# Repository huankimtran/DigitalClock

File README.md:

# DigitalClock
Code, PCB layout and schematic for a digital clock

Working video
https://www.facebook.com/HuanKimTran/videos/448578368496452/?hc_location=ufi

Project images

https://www.facebook.com/media/set/?set=a.436338533053769&type=1&l=68016e3bc0

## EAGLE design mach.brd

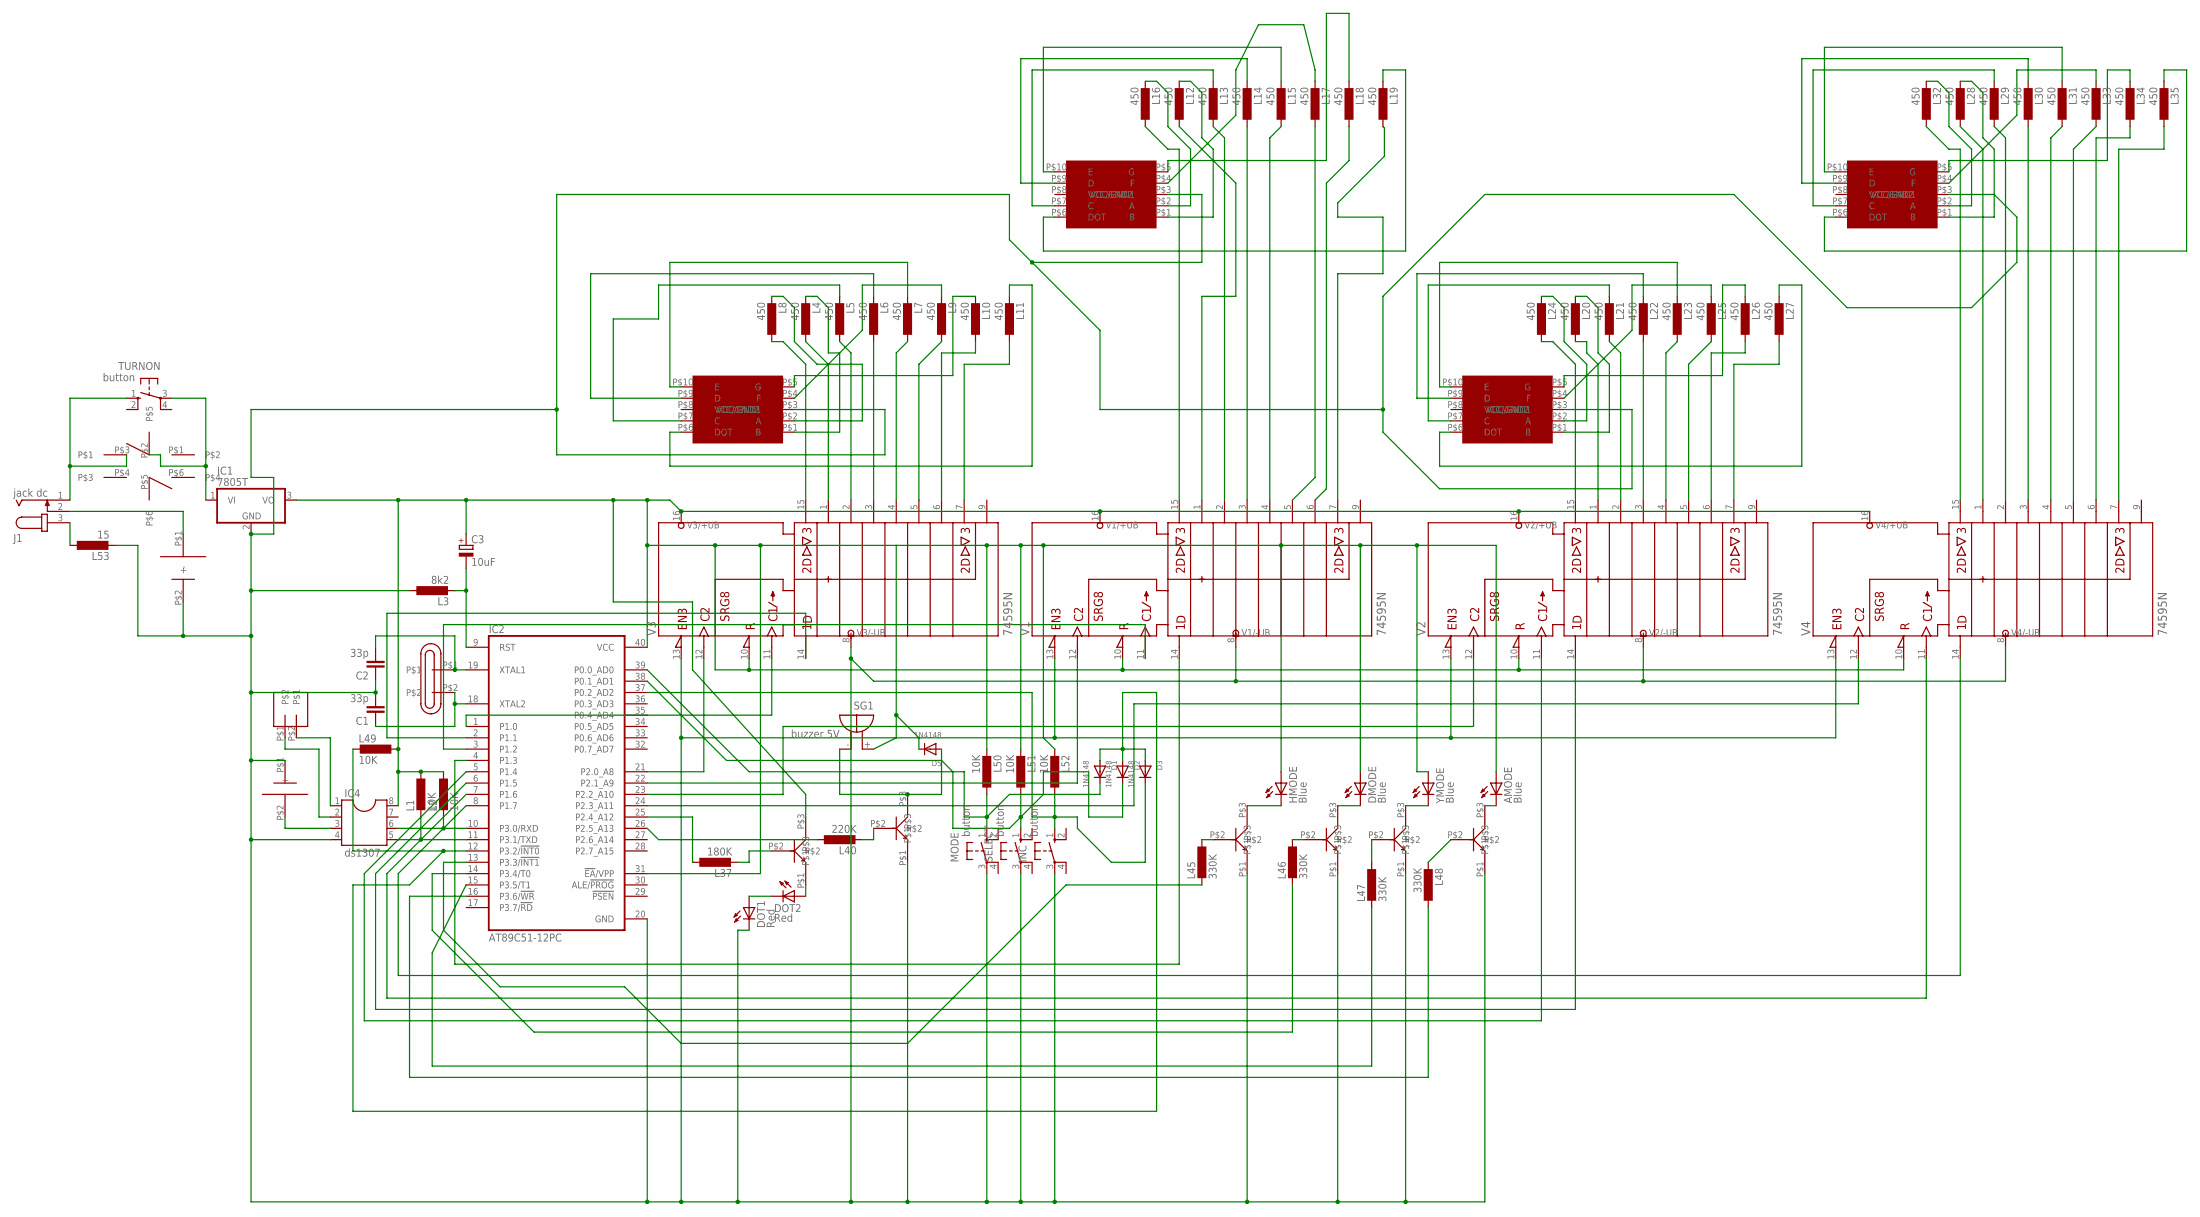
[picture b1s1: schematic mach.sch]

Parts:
7SEG1, 7SEG2, 7SEG3, 7SEG4: 7SEG13X19 common Katot; 7SEG13X19
AMODE: Blue; LED5MM
C1, C2: 33p; C5B3
C3: 10uF; E2-5
D1, D2, D3, D5: 1N4148; DO-1N4148
DMODE: Blue; LED5MM
DOT1, DOT2: Red; LED5MM
HMODE: Blue; LED5MM
IC1: 7805T; TO220H
IC2: AT89C51-12PC; DIL40
IC4: ds1307; DIL08
INC: button; B3F-10XX
J1: jack dc; SPC4077
L1, L2, L49, L50, L51, L52: 10K; 0207/10
L3: 8k2; 0207/10
L4, L5, L6, L7, L8, L9, L10, L11, L12, L13, L14, L15, L16, L17, L18, L19, L20, L21, L22, L23, L24, L25, L26, L27, L28, L29, L30, L31, L32, L33, L34, L35: 450; 0207/10
L37: 180K; 0207/10
L40: 220K; 0207/10
L45, L46, L47, L48: 330K; 0207/10
L53: 15; 0207/10
MODE: button; B3F-10XX
SELECT: button; B3F-10XX
SG1: buzzer 5V; BMT1205XH7.5
TURNON: button; B3F-10XX
U$1: PINCMOS3VCR23
U$2: XTAL32KHZMINI
U$5: XTAL12MHZ
U$7: lock button down; PUSKLOCKBUTTON
U$8, U$9, U$10, U$11, U$12, U$13: C9014
U$14: 9V; 9VBATERYJACK
V1, V2, V3, V4: 74595N; DIL16
YMODE: Blue; LED5MM

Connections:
ET: J1.2, U$14.P$1 (+)
GND: 7SEG1.P$3 (VCC/GND1), 7SEG2.P$3 (VCC/GND1), 7SEG3.P$3 (VCC/GND1), 7SEG4.P$3 (VCC/GND1), C1.2, C2.1, DOT1.K (C), IC1.2 (GND), IC2.20 (GND), IC4.4, INC.3, L3.1, L53.2, MODE.3, SELECT.3, U$1.P$1 (-), U$8.P$1, U$9.P$1, U$10.P$1, U$11.P$1, U$12.P$1, U$14.P$2 (-), V1.8 (-UB), V1.13 (!G), V2.8 (-UB), V2.13 (!G), V3.8 (-UB), V3.13 (!G), V4.8 (-UB), V4.13 (!G)
unnamed: IC2.11 (P3.1/TXD), IC4.5, L1.2
unnamed: IC2.10 (P3.0/RXD), IC4.6, L2.2
unnamed: IC4.1, U$2.P$2
unnamed: C3.-, IC2.9 (RST), L3.2
unnamed: IC4.3, U$1.P$2 (+)
unnamed: IC4.2, U$2.P$1
unnamed: C2.2, IC2.19 (XTAL1), U$5.P$1
unnamed: C1.1, IC2.18 (XTAL2), U$5.P$2
unnamed: D1.C, IC2.39 (P0.0_AD0), L50.1, MODE.1 (S)
unnamed: IC2.25 (P2.4_A12), L37.1
unnamed: IC2.1 (P1.0), V3.11 (SRCK)
unnamed: IC2.2 (P1.1), V3.14 (SER)
unnamed: IC2.3 (P1.2), V1.11 (SRCK)
unnamed: DOT2.A, U$13.P$1
unnamed: IC2.5 (P1.4), V2.11 (SRCK)
unnamed: 7SEG1.P$4 (F), L9.2
unnamed: IC2.6 (P1.5), V2.14 (SER)
unnamed: IC2.7 (P1.6), V4.11 (SRCK)
unnamed: IC2.8 (P1.7), V4.14 (SER)
unnamed: L4.1, V3.1 (QB)
unnamed: L8.1, V3.15 (QA)
unnamed: 7SEG1.P$10 (E), L7.2
unnamed: L9.1, V3.5 (QF)
unnamed: L10.1, V3.6 (QG)
unnamed: 7SEG1.P$1 (B), L4.2
unnamed: L11.1, V3.7 (QH)
unnamed: L6.1, V3.3 (QD)
unnamed: L7.1, V3.4 (QE)
unnamed: L5.1, V3.2 (QC)
unnamed: DOT1.A, DOT2.K (C)
unnamed: J1.1, TURNON.1 (S), U$7.P$3
unnamed: 7SEG1.P$5 (G), L10.2
unnamed: IC2.4 (P1.3), V1.14 (SER)
unnamed: 7SEG1.P$6 (DOT), L11.2
unnamed: IC1.1 (VI), TURNON.3, U$7.P$2
unnamed: 7SEG2.P$10 (E), L15.2
unnamed: L13.1, V1.2 (QC)
unnamed: L14.1, V1.3 (QD)
unnamed: L15.1, V1.4 (QE)
unnamed: L17.1, V1.5 (QF)
unnamed: 7SEG2.P$5 (G), L18.2
unnamed: L18.1, V1.6 (QG)
unnamed: L16.1, V1.15 (QA)
unnamed: 7SEG2.P$2 (A), L16.2
unnamed: 7SEG2.P$7 (C), L13.2
unnamed: 7SEG2.P$9 (D), L14.2
unnamed: 7SEG2.P$6 (DOT), L19.2
unnamed: L37.2, U$13.P$2
unnamed: 7SEG3.P$10 (E), L23.2
unnamed: L27.1, V2.7 (QH)
unnamed: L25.1, V2.5 (QF)
unnamed: L26.1, V2.6 (QG)
unnamed: 7SEG3.P$6 (DOT), L27.2
unnamed: L23.1, V2.4 (QE)
unnamed: L21.1, V2.2 (QC)
unnamed: L20.1, V2.1 (QB)
unnamed: L24.1, V2.15 (QA)
unnamed: 7SEG3.P$2 (A), L24.2
unnamed: 7SEG3.P$1 (B), L20.2
unnamed: 7SEG3.P$7 (C), L21.2
unnamed: 7SEG3.P$9 (D), L22.2
unnamed: 7SEG3.P$4 (F), L25.2
unnamed: 7SEG3.P$5 (G), L26.2
unnamed: L22.1, V2.3 (QD)
unnamed: 7SEG4.P$10 (E), L31.2
unnamed: L35.1, V4.7 (QH)
unnamed: L33.1, V4.5 (QF)
unnamed: L34.1, V4.6 (QG)
unnamed: L30.1, V4.3 (QD)
unnamed: L31.1, V4.4 (QE)
unnamed: L29.1, V4.2 (QC)
unnamed: L28.1, V4.1 (QB)
unnamed: L32.1, V4.15 (QA)
unnamed: 7SEG4.P$2 (A), L32.2
unnamed: 7SEG4.P$1 (B), L28.2
unnamed: 7SEG4.P$7 (C), L29.2
unnamed: 7SEG4.P$9 (D), L30.2
unnamed: 7SEG4.P$4 (F), L33.2
unnamed: 7SEG4.P$5 (G), L34.2
unnamed: 7SEG4.P$6 (DOT), L35.2
unnamed: IC2.26 (P2.5_A13), L40.1
unnamed: L40.2, U$8.P$2
unnamed: L45.1, U$10.P$2
unnamed: L46.1, U$9.P$2
unnamed: L47.1, U$11.P$2
unnamed: HMODE.K (C), U$10.P$3
unnamed: D5.A, SG1.-, U$8.P$3
unnamed: D3.C, IC2.37 (P0.2_AD2), INC.1 (S), L52.1
unnamed: L48.2, U$12.P$2
unnamed: AMODE.K (C), U$12.P$3
unnamed: U$11.P$3, YMODE.K (C)
unnamed: DMODE.K (C), U$9.P$3
unnamed: IC2.13 (P3.3/!INT1), L45.2
unnamed: D1.A, D2.A, D3.A, IC2.12 (P3.2/!INT0), L49.2
unnamed: IC2.14 (P3.4/T0), L46.2
unnamed: IC2.15 (P3.5/T1), L47.2
unnamed: IC2.16 (P3.6/!WR), L48.1
unnamed: IC2.21 (P2.0_A8), V3.12 (RCK)
unnamed: IC2.22 (P2.1_A9), V1.12 (RCK)
unnamed: IC2.23 (P2.2_A10), V2.12 (RCK)
unnamed: IC2.24 (P2.3_A11), V4.12 (RCK)
unnamed: J1.3, L53.1
unnamed: D2.C, IC2.38 (P0.1_AD1), L51.1, SELECT.1 (S)
unnamed: 7SEG1.P$2 (A), L8.2
unnamed: 7SEG1.P$9 (D), L6.2
unnamed: 7SEG2.P$4 (F), L17.2
unnamed: 7SEG1.P$7 (C), L5.2
unnamed: L19.1, V1.7 (QH)
unnamed: L12.1, V1.1 (QB)
unnamed: 7SEG2.P$1 (B), L12.2
VCC: AMODE.A, C3.+, D5.C, DMODE.A, HMODE.A, IC1.3 (VO), IC2.31 (!EA!/VPP), IC2.40 (VCC), IC4.8, L1.1, L2.1, L49.1, L50.2, L51.2, L52.2, SG1.+, U$13.P$3, V1.10 (!SRCLR), V1.16 (+UB), V2.10 (!SRCLR), V2.16 (+UB), V3.10 (!SRCLR), V3.16 (+UB), V4.10 (!SRCLR), V4.16 (+UB), YMODE.A

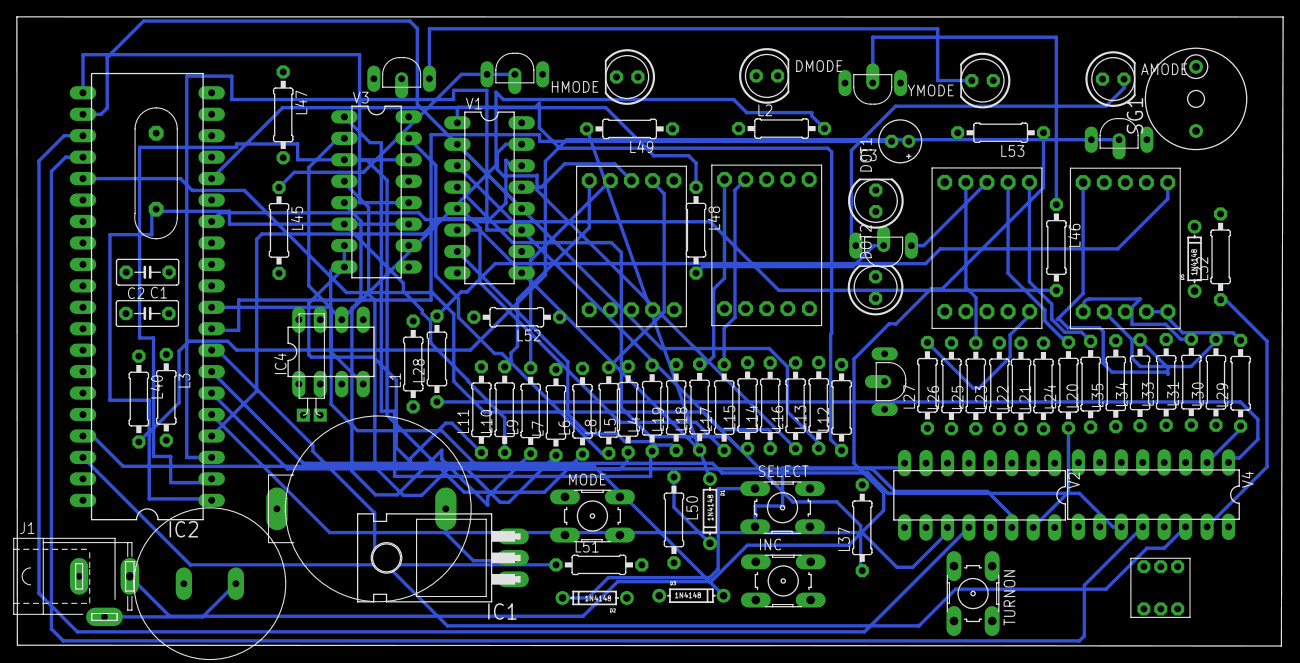
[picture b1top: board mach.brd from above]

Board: 2 copper layers, 150.0 x 74.5 mm, 87 parts (0 on the bottom side), 113 nets.
